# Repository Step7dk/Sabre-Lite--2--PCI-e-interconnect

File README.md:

# Sabre Lite -2- PCI-e interconnect

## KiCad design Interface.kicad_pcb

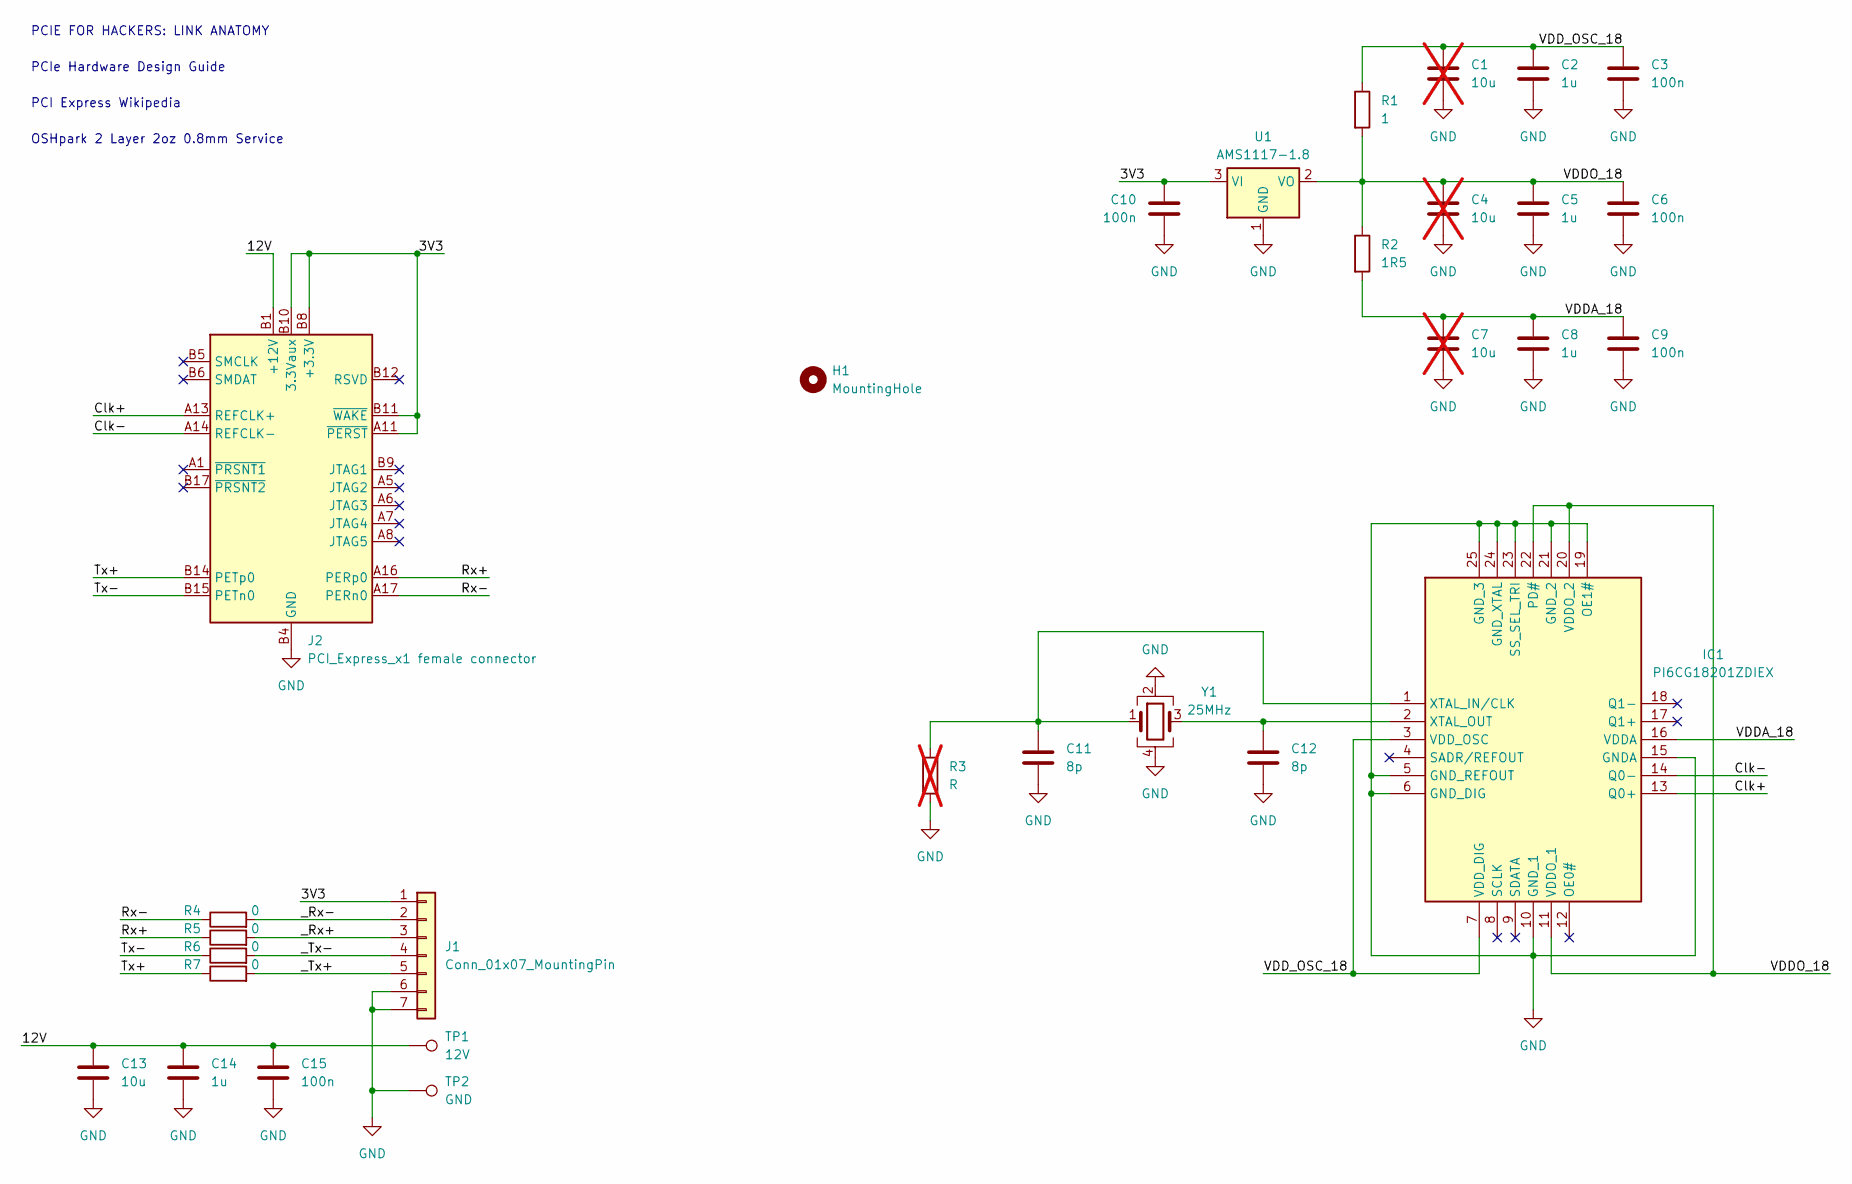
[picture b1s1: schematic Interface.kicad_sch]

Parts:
C1, C4, C7: 10u; C_0603_1608Metric_Pad1.08x0.95mm_HandSolder; not fitted
C2, C5, C8, C14: 1u; C_0603_1608Metric_Pad1.08x0.95mm_HandSolder
C3, C6, C9, C10, C15: 100n; C_0603_1608Metric_Pad1.08x0.95mm_HandSolder
C11, C12: 8p; C_0603_1608Metric_Pad1.08x0.95mm_HandSolder
C13: 10u; C_0603_1608Metric_Pad1.08x0.95mm_HandSolder
H1: MountingHole; MountingHole_3.2mm_M3_ISO14580
IC1: PI6CG18201ZDIEX; QFN-24-1EP_4x4mm_P0.5mm_EP2.6x2.6mm; Mouser Part Number 729-PI6CG18201ZDIEX
J1: Conn_01x07_MountingPin; Molex_PicoBlade_53047-0710_1x07_P1.25mm_Vertical
J2: PCI_Express_x1 female connector; PCIE03602FDTH; Partnr PCIE-036-02-F-D-TH
R1: 1; R_0603_1608Metric_Pad0.98x0.95mm_HandSolder
R2: 1R5; R_0603_1608Metric_Pad0.98x0.95mm_HandSolder
R3: R; R_0603_1608Metric_Pad0.98x0.95mm_HandSolder; not fitted
R4, R5, R6, R7: 0; R_0402_1005Metric_Pad0.72x0.64mm_HandSolder
TP1: 12V; TestPoint_THTPad_D2.5mm_Drill1.2mm
TP2: GND; TestPoint_THTPad_D2.5mm_Drill1.2mm
U1: AMS1117-1.8; SOT-223-3_TabPin2
Y1: 25MHz; Crystal_SMD_SeikoEpson_TSX3225-4Pin_3.2x2.5mm_HandSoldering; Manufacturer_Part_Number TSX-3225 25.0000MF20X-AJ; Mouser Part Number 732-TSX-32525MF2X-AJ

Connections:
/3V3: C10.1, J1.1, J2.A9 (+3.3V), J2.A10 (+3.3V), J2.A11 (~PERST), J2.B8 (+3.3V), J2.B10 (3.3Vaux), J2.B11 (~WAKE), U1.3 (VI)
/12V: C13.1, C14.1, C15.1, J2.A2 (+12V), J2.A3 (+12V), J2.B1 (+12V), J2.B2 (+12V), J2.B3 (+12V), TP1.1
/Clk+: IC1.13 (Q0+), J2.A13 (REFCLK+)
/Clk-: IC1.14 (Q0-), J2.A14 (REFCLK-)
/Rx+: J2.A16 (PERp0), R5.1
/Rx-: J2.A17 (PERn0), R4.1
/Tx+: J2.B14 (PETp0), R7.1
/Tx-: J2.B15 (PETn0), R6.1
/VDDA_18: C7.1, C8.1, C9.1, IC1.16 (VDDA), R2.2
/VDDO_18: C4.1, C5.1, C6.1, IC1.11 (VDDO_1), IC1.20 (VDDO_2), IC1.22 (PD#), R1.2, R2.1, U1.2 (VO)
/VDD_OSC_18: C1.1, C2.1, C3.1, IC1.3 (VDD_OSC), IC1.7 (VDD_DIG), R1.1
/_Rx+: J1.3, R5.2
/_Rx-: J1.2, R4.2
/_Tx+: J1.5, R7.2
/_Tx-: J1.4, R6.2
GND: C1.2, C2.2, C3.2, C4.2, C5.2, C6.2, C7.2, C8.2, C9.2, C10.2, C11.2, C12.2, C13.2, C14.2, C15.2, IC1.5 (GND_REFOUT), IC1.6 (GND_DIG), IC1.10 (GND_1), IC1.15 (GNDA), IC1.19 (OE1#), IC1.21 (GND_2), IC1.23 (SS_SEL_TRI), IC1.24 (GND_XTAL), IC1.25 (GND_3), J1.6, J1.7, J2.A4 (GND), J2.A12 (GND), J2.A15 (GND), J2.A18 (GND), J2.B4 (GND), J2.B7 (GND), J2.B13 (GND), J2.B16 (GND), J2.B18 (GND), R3.2, TP2.1, U1.1 (GND), Y1.2, Y1.4
unnamed: C11.1, IC1.1 (XTAL_IN/CLK), R3.1, Y1.1
unnamed: C12.1, IC1.2 (XTAL_OUT), Y1.3

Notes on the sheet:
PCIE FOR HACKERS: LINK ANATOMY
PCI Express Wikipedia
PCIe Hardware Design Guide
OSHpark 2 Layer 2oz 0.8mm Service

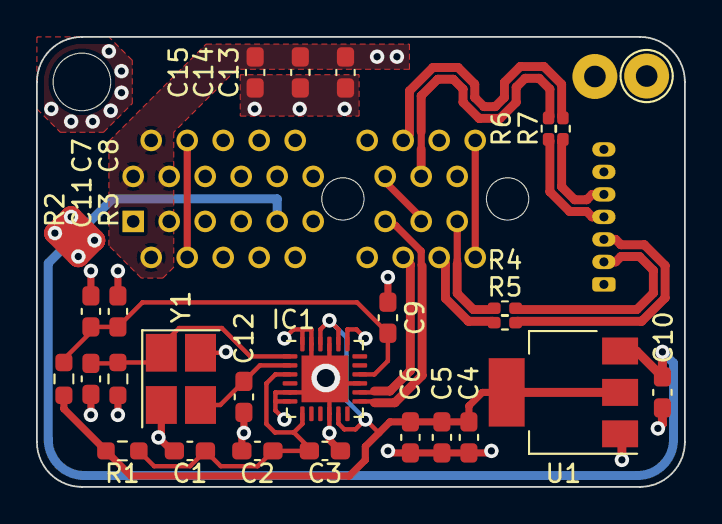
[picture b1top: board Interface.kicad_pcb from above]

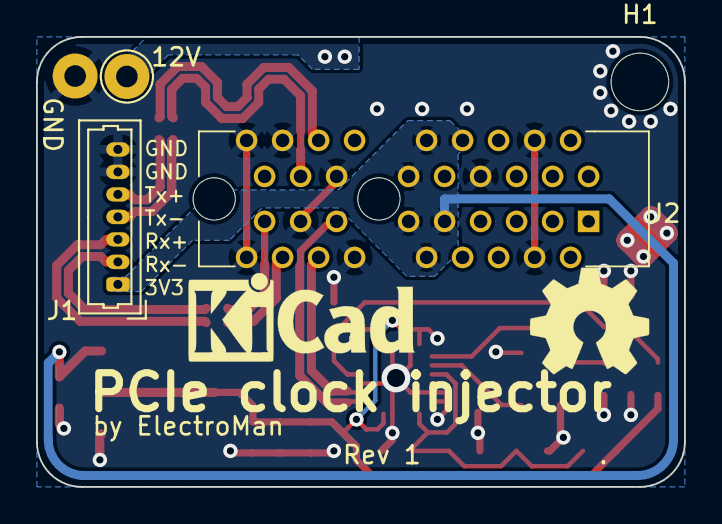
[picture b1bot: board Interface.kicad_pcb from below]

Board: 2 copper layers, 36.0 x 25.0 mm, 30 parts (4 on the bottom side), 18 nets.

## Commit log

2023-12-13 Unlock files
2023-12-14 Add few details
2023-12-17 Layout
2023-12-17 Continue layout
2023-12-18 Layout finished
2024-06-23 As ordered with OSHpark
2024-08-27 Add ibom
2024-09-05 ignore kicad_prl
